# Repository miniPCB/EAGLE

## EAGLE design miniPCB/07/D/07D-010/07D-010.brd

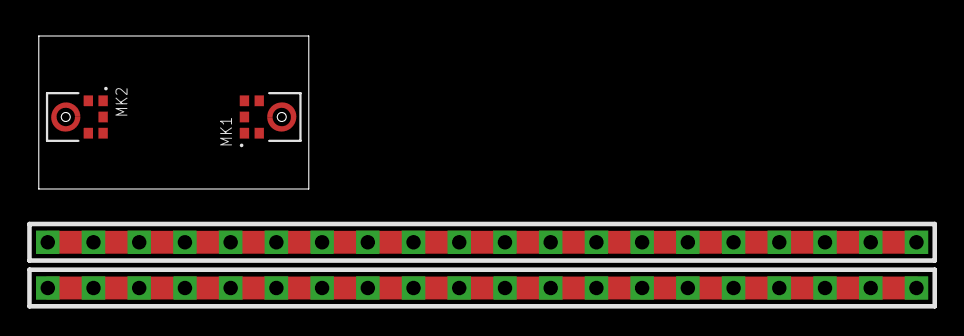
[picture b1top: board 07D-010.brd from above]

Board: 2 copper layers, 15.0 x 8.5 mm, 3 parts (0 on the bottom side), 2 nets, no tracks yet.

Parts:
MK1, MK2: SPH0645LM4H-B; MIC_SPH0645LM4H-B
U$1: BTM525; PINS_1_20P

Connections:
GND: MK1.3, MK2.3
VDD: MK1.5, MK2.5

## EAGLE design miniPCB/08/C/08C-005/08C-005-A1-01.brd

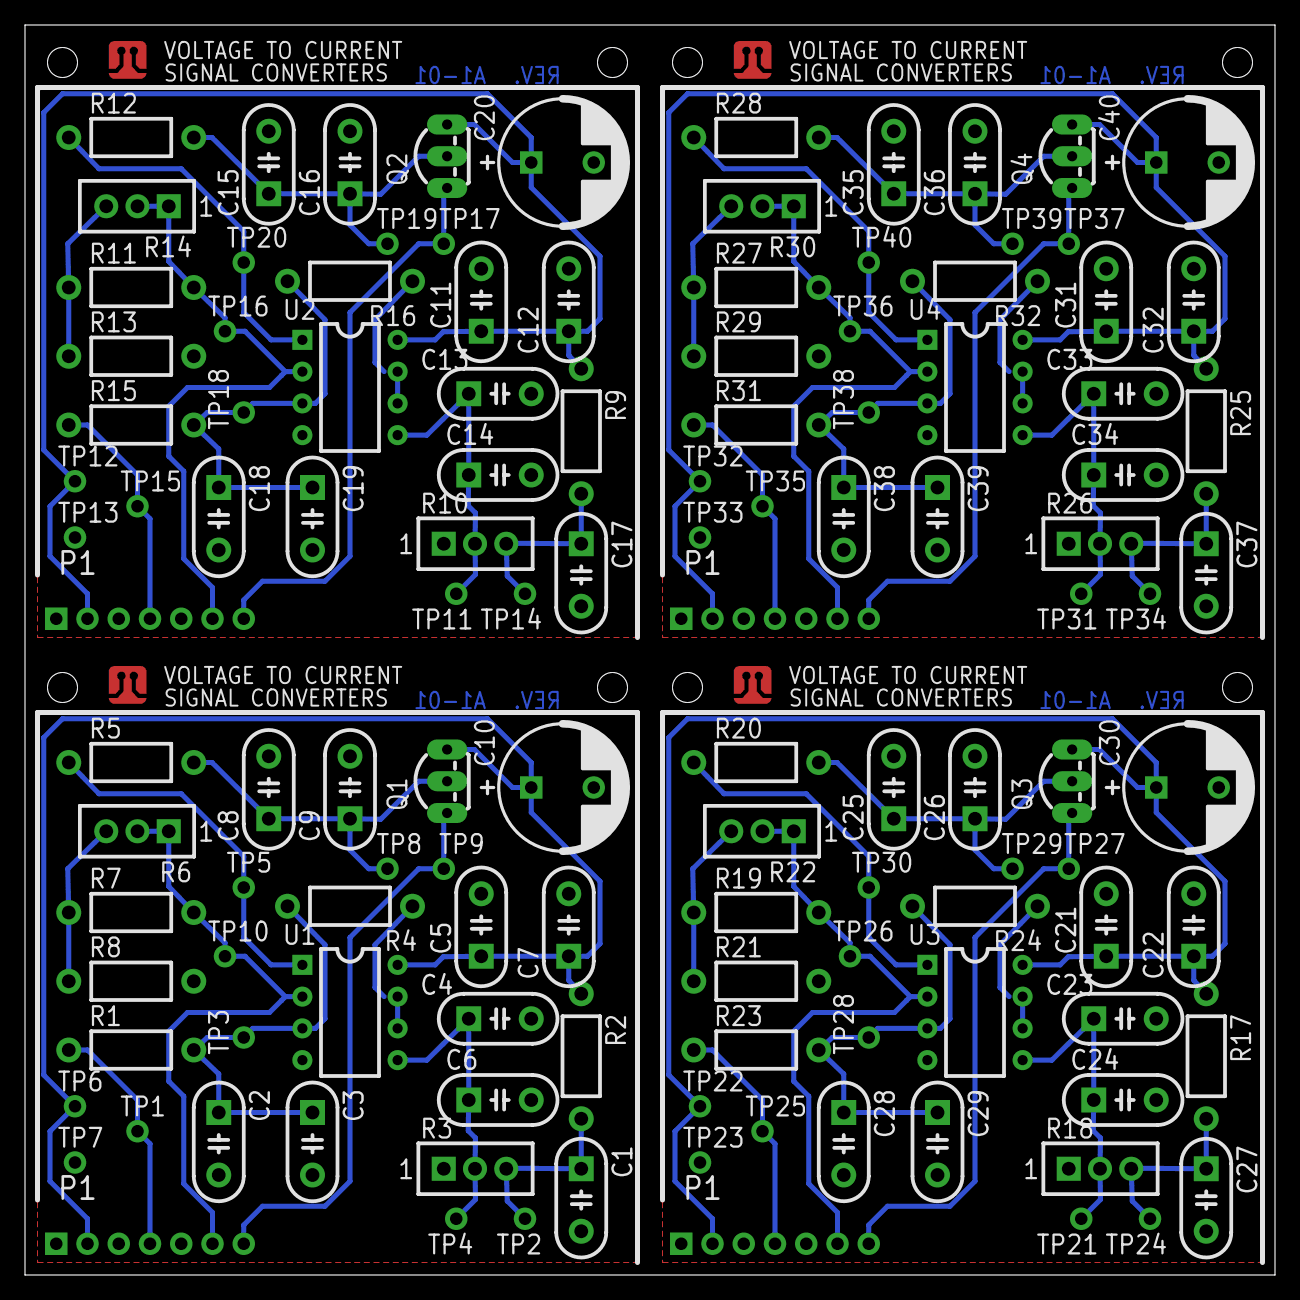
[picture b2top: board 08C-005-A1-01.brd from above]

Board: 2 copper layers, 100.0 x 100.0 mm, 129 parts (0 on the bottom side), 48 nets.

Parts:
C1, C2, C3, C4, C5, C6, C7, C8, C9, C11, C12, C13, C14, C15, C16, C17, C18, C19, C21, C22, C23, C24, C25, C26, C27, C28, C29, C31, C32, C33, C34, C35, C36, C37, C38, C39: C050-024X044
C10, C20, C30, C40: C5MM
E$1: MINIPCB_PANEL_IMAGEFRAME
P1, P2, P3, P4: PINS_1X7
PCB1, PCB2, PCB3, PCB4: MINIPCB_0P_50X50MM
Q1, Q2, Q3, Q4: TO92-EBC-OVAL
R1, R2, R4, R5, R7, R8, R9, R11, R12, R13, R15, R16, R17, R19, R20, R21, R23, R24, R25, R27, R28, R29, R31, R32: 0207/10
R3, R6, R10, R14, R18, R22, R26, R30: TRIM_0100
TP1, TP2, TP3, TP4, TP5, TP6, TP7, TP8, TP9, TP10, TP11, TP12, TP13, TP14, TP15, TP16, TP17, TP18, TP19, TP20, TP21, TP22, TP23, TP24, TP25, TP26, TP27, TP28, TP29, TP30, TP31, TP32, TP33, TP34, TP35, TP36, TP37, TP38, TP39, TP40: PINS_1_TESTPOINT_KE5000_NOTEXT
U1, U2, U3, U4: DIL08

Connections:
BIAS: C4.1, C6.1, R3.2, TP4.1, U1.5
BIAS1: C13.1, C14.1, R10.2, TP11.1, U2.5
BIAS2: C23.1, C24.1, R18.2, TP21.1, U3.5
BIAS3: C33.1, C34.1, R26.2, TP31.1, U4.5
GND: C1.2, C2.2, C3.2, C4.2, C5.2, C6.2, C7.2, C8.2, C9.2, C10.-, P1.1, P1.5, R3.1, R8.2, TP7.1, U1.4
GND1: C11.2, C12.2, C13.2, C14.2, C15.2, C16.2, C17.2, C18.2, C19.2, C20.-, P2.1, P2.5, R10.1, R13.2, TP13.1, U2.4
GND2: C21.2, C22.2, C23.2, C24.2, C25.2, C26.2, C27.2, C28.2, C29.2, C30.-, P3.1, P3.5, R18.1, R21.2, TP23.1, U3.4
GND3: C31.2, C32.2, C33.2, C34.2, C35.2, C36.2, C37.2, C38.2, C39.2, C40.-, P4.1, P4.5, R26.1, R29.2, TP33.1, U4.4
IN: R4.1, U1.6, U1.7
IN1: R16.1, U2.6, U2.7
IN2: R24.1, U3.6, U3.7
IN3: R32.1, U4.6, U4.7
unnamed: C2.1, C3.1, R1.2, R4.2, TP3.1, U1.3
unnamed: P1.4, R1.1, TP1.1
unnamed: P2.4, R15.1, TP15.1
unnamed: C18.1, C19.1, R15.2, R16.2, TP18.1, U2.3
unnamed: P3.4, R23.1, TP25.1
unnamed: C28.1, C29.1, R23.2, R24.2, TP28.1, U3.3
unnamed: P4.4, R31.1, TP35.1
unnamed: C38.1, C39.1, R31.2, R32.2, TP38.1, U4.3
OUT+: P1.7, Q1.E, TP9.1
OUT+1: P2.7, Q2.E, TP17.1
OUT+2: P3.7, Q3.E, TP27.1
OUT+3: P4.7, Q4.E, TP37.1
OUT-: P1.6, R6.1, R6.2, R7.2, TP10.1, U1.2
OUT-1: P2.6, R11.2, R14.1, R14.2, TP16.1, U2.2
OUT-2: P3.6, R19.2, R22.1, R22.2, TP26.1, U3.2
OUT-3: P4.6, R27.2, R30.1, R30.2, TP36.1, U4.2
Q1.B: C8.1, C9.1, Q1.B, R5.2, TP8.1
Q1.B1: C15.1, C16.1, Q2.B, R12.2, TP19.1
Q1.B2: C25.1, C26.1, Q3.B, R20.2, TP29.1
Q1.B3: C35.1, C36.1, Q4.B, R28.2, TP39.1
R2.1: C17.1, R9.2, R10.3, TP14.1
R2.2: C27.1, R17.2, R18.3, TP24.1
R2.3: C1.1, R2.2, R3.3, TP2.1
R2.4: C37.1, R25.2, R26.3, TP34.1
R6.1: R11.1, R13.1, R14.3
R6.2: R19.1, R21.1, R22.3
R6.3: R6.3, R7.1, R8.1
R6.4: R27.1, R29.1, R30.3
U1.1: R5.1, TP5.1, U1.1
U1.2: R12.1, TP20.1, U2.1
U1.3: R20.1, TP30.1, U3.1
U1.4: R28.1, TP40.1, U4.1
V+: C5.1, C7.1, C10.+, P1.2, Q1.C, R2.1, TP6.1, U1.8
V+1: C11.1, C12.1, C20.+, P2.2, Q2.C, R9.1, TP12.1, U2.8
V+2: C21.1, C22.1, C30.+, P3.2, Q3.C, R17.1, TP22.1, U3.8
V+3: C31.1, C32.1, C40.+, P4.2, Q4.C, R25.1, TP32.1, U4.8

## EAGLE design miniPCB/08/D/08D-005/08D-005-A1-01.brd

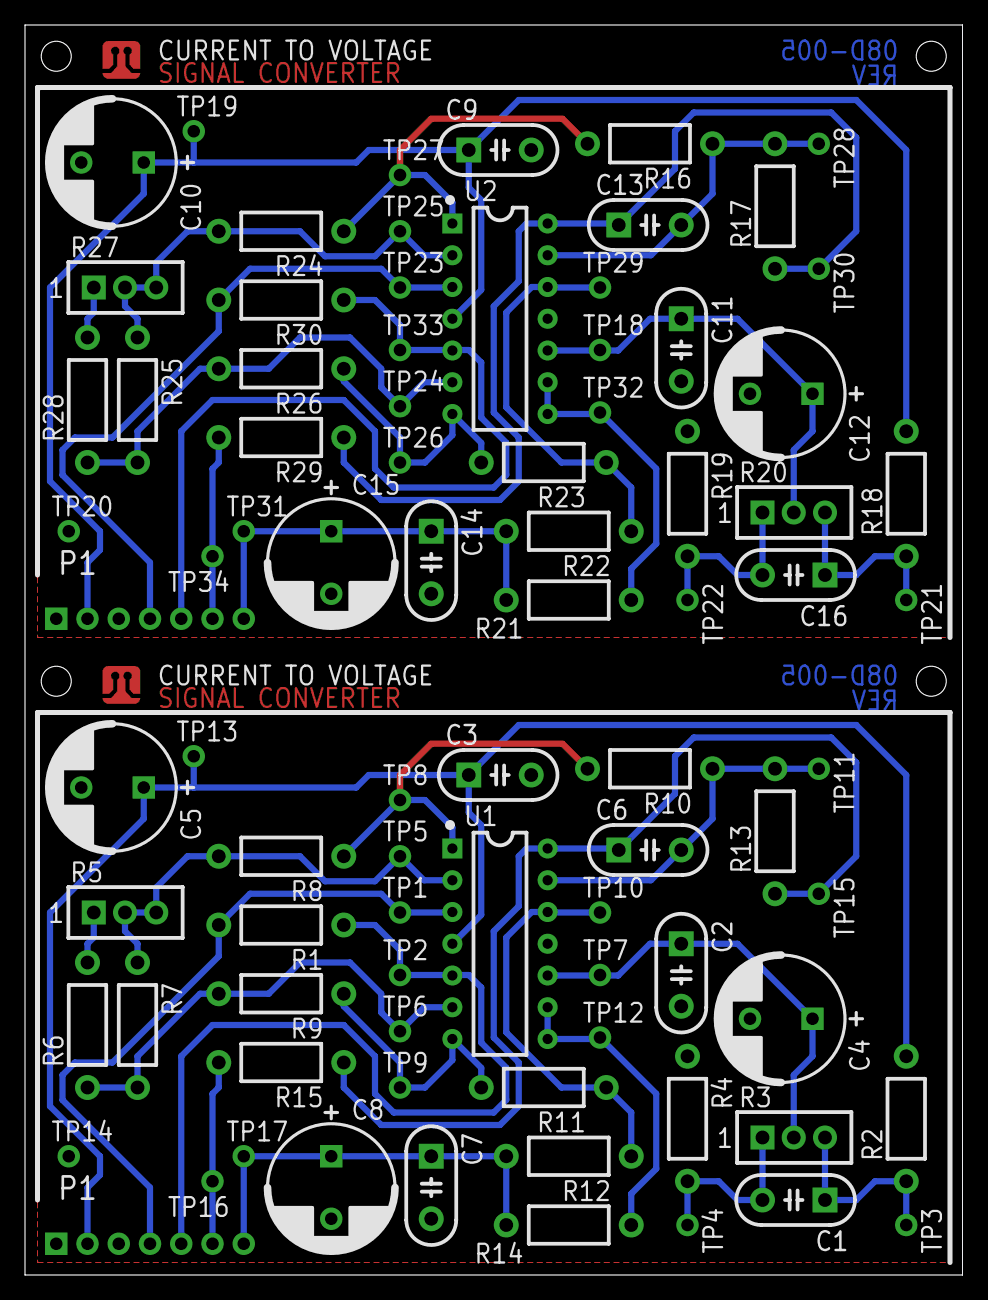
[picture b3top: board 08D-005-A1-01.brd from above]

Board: 2 copper layers, 75.0 x 100.0 mm, 87 parts (0 on the bottom side), 36 nets.

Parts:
C1, C2, C3, C6, C7, C9, C11, C13, C14, C16: C050-024X044
C4, C5, C8, C10, C12, C15: C5MM
E$1: MINIPCB_PANEL_IMAGEFRAME
P1, P2: PINS_1X7
PCB1, PCB2: MINIPCB_0P_50X75
R1, R2, R4, R6, R7, R8, R9, R10, R11, R12, R13, R14, R15, R16, R17, R18, R19, R21, R22, R23, R24, R25, R26, R28, R29, R30: 0207/10
R3, R5, R20, R27: TRIM_0100
TP1, TP2, TP3, TP4, TP5, TP6, TP7, TP8, TP9, TP10, TP11, TP12, TP13, TP14, TP15, TP16, TP17, TP18, TP19, TP20, TP21, TP22, TP23, TP24, TP25, TP26, TP27, TP28, TP29, TP30, TP31, TP32, TP33, TP34: PINS_1_TESTPOINT_KE5000_NOTEXT
U1, U2: DIL14

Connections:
BIAS: C2.1, C4.+, R3.2, TP7.1, U1.10
BIAS1: C11.1, C12.+, R20.2, TP18.1, U2.10
GND: C2.2, C3.2, C4.-, C5.-, C7.2, C8.-, P1.1, R4.1, TP14.1, U1.11
GND1: C9.2, C10.-, C11.2, C12.-, C14.2, C15.-, P2.1, R19.1, TP20.1, U2.11
unnamed: R11.1, R12.1, TP10.1, U1.12
unnamed: C7.1, C8.+, P1.7, R12.2, R14.2, TP17.1
unnamed: P1.5, R1.1, TP2.1, U1.5
unnamed: P1.4, R1.2, TP1.1, U1.3
unnamed: R5.2, R5.3, R7.1, R8.2, TP5.1, U1.2
unnamed: R6.1, R7.2, R9.2, TP6.1, U1.6
unnamed: R8.1, R10.2, TP8.1, U1.1
unnamed: R9.1, R11.2, TP9.1, U1.7
unnamed: R14.1, TP12.1, U1.8, U1.9
unnamed: R5.1, R6.2
unnamed: P1.6, R15.2, TP16.1
unnamed: R22.1, R23.1, TP29.1, U2.12
unnamed: C14.1, C15.+, P2.7, R21.2, R22.2, TP31.1
unnamed: P2.5, R30.1, TP33.1, U2.5
unnamed: P2.4, R30.2, TP23.1, U2.3
unnamed: R24.2, R25.1, R27.2, R27.3, TP25.1, U2.2
unnamed: R25.2, R26.2, R28.1, TP24.1, U2.6
unnamed: R16.2, R24.1, TP27.1, U2.1
unnamed: R23.2, R26.1, TP26.1, U2.7
unnamed: R21.1, TP32.1, U2.8, U2.9
unnamed: R27.1, R28.2
unnamed: P2.6, R29.2, TP34.1
OUT: C6.1, R13.1, R15.1, TP15.1, U1.14
OUT1: C13.1, R17.1, R29.1, TP30.1, U2.14
POT.1: C1.2, R3.1, R4.2, TP4.1
POT.2: C16.1, R18.1, R20.3, TP21.1
POT.3: C1.1, R2.1, R3.3, TP3.1
POT.4: C16.2, R19.2, R20.1, TP22.1
V+: C3.1, C5.+, P1.2, R2.2, TP13.1, U1.4
V+1: C9.1, C10.+, P2.2, R18.2, TP19.1, U2.4
VFB: C6.2, R10.1, R13.2, TP11.1, U1.13
VFB1: C13.2, R16.1, R17.2, TP28.1, U2.13

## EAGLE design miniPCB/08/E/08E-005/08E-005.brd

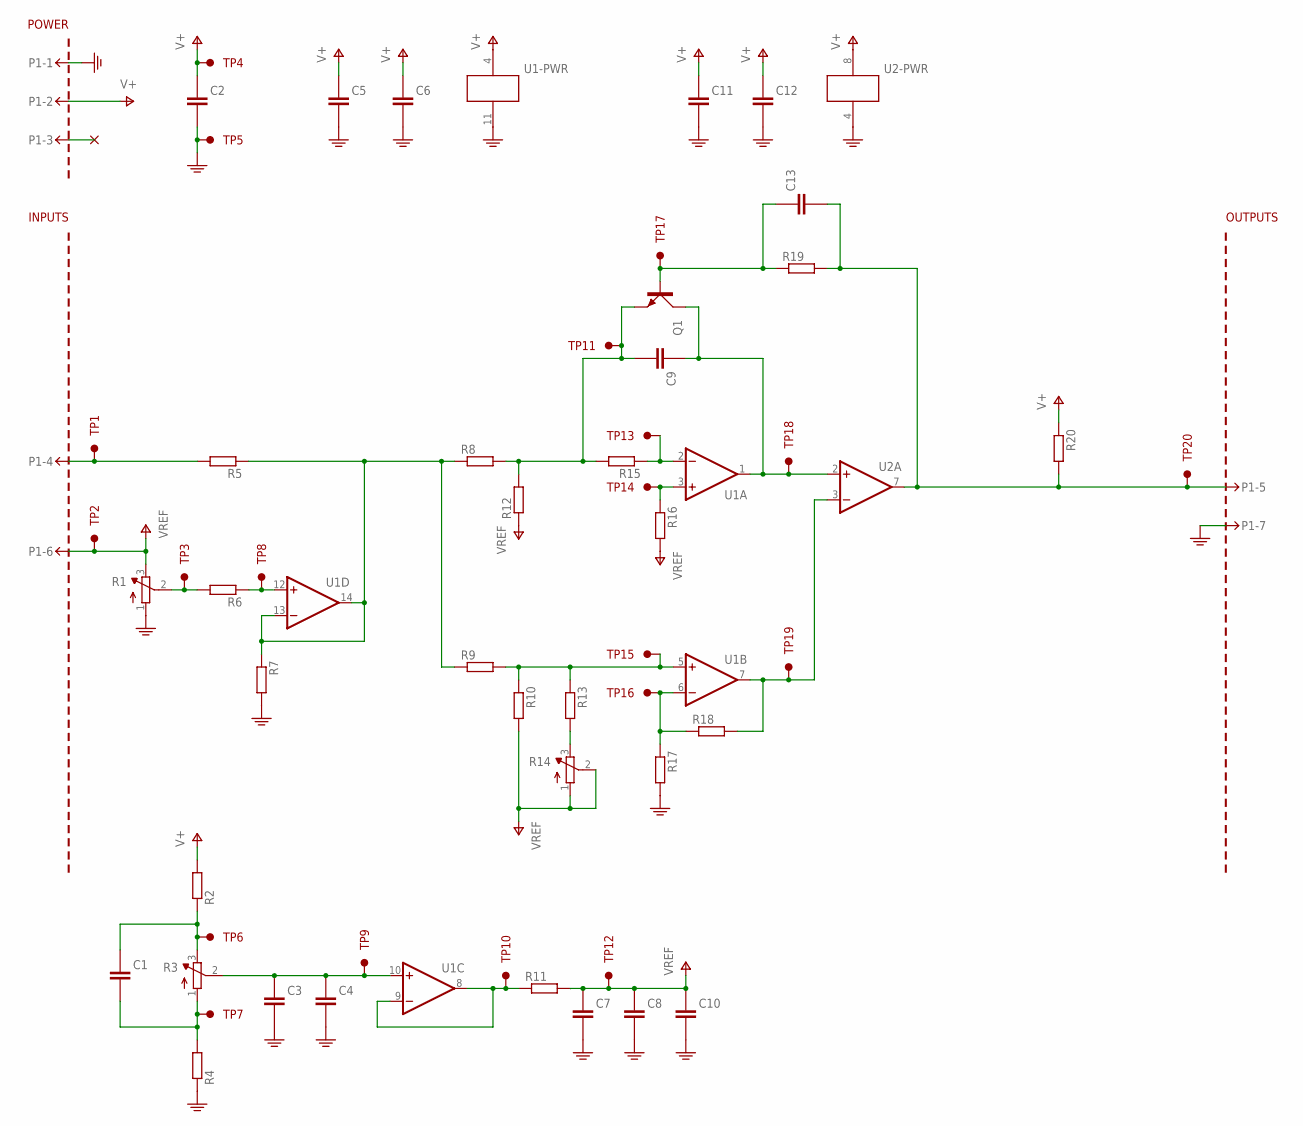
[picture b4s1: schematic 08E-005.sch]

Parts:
C1, C3, C4, C5, C6, C7, C8, C9, C11, C12, C13: CAPACITORTHD; C050-024X044
C2, C10: CAPACITOR_10; C5MM
P1-: MINIPCB_7P50X100; MINIPCB_7P_50X100; PART_NUMBER X08E-005-A
Q1: BJT_NPNEBC; TO92-EBC-OVAL
R1: TRIMPOT3386; TRIM-3386
R2, R4, R5, R6, R7, R8, R9, R10, R11, R12, R13, R15, R16, R17, R18, R19, R20: RESISTOR10MM; 0207/10
R3, R14: TRIMPOT0.100THD; TRIM_0100
TP1, TP2, TP3, TP4, TP5, TP6, TP7, TP8, TP9, TP10, TP11, TP12, TP13, TP14, TP15, TP16, TP17, TP18, TP19, TP20: TESTPOINTKE5000-SMTEXT; PINS_1_TESTPOINT_KE5000_NOTEXT
U1: OPAMP_QUADTHD; DIL14
U2: COMPARATOR_SINGLE_WITHBALANCETHD; DIL08

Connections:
BIAS: C3.1 (+), C4.1 (+), R3.2 (S), TP9.1, U1.10 (+IN)
GND: C2.-, C3.2 (-), C4.2 (-), C5.2 (-), C6.2 (-), C7.2 (-), C8.2 (-), C10.-, C11.2 (-), C12.2 (-), P1-.1, P1-.7, R1.1 (A), R4.1, R7.2, R17.2, TP5.1, U1.11 (V-), U2.4 (V-); also elsewhere on the board
unnamed: R16.1, TP14.1, U1.3 (+IN)
unnamed: R15.1, TP13.1, U1.2 (-IN)
unnamed: C9.2 (-), Q1.E, R8.2, R12.2, R15.2, TP11.1
unnamed 5: C13.2 (-), P1-.5, R19.2, R20.2, TP20.1, U2.7 (OUT); also elsewhere on the board
unnamed: C9.1 (+), Q1.C, TP18.1, U1.1 (OUT), U2.2 (+IN)
unnamed: C13.1 (+), Q1.B, R19.1, TP17.1
unnamed: R11.1, TP10.1, U1.8 (OUT), U1.9 (-IN)
unnamed: R17.1, R18.1, TP16.1, U1.6 (-IN)
unnamed: R18.2, TP19.1, U1.7 (OUT), U2.3 (-IN)
unnamed: R6.1, TP8.1, U1.12 (+IN)
unnamed: R1.2 (S), R6.2, TP3.1
unnamed: R9.2, R10.1, R13.1, TP15.1, U1.5 (+IN)
unnamed: R13.2, R14.3 (E)
POT.1: C1.2 (-), R3.1 (A), R4.2, TP7.1
POT.3: C1.1 (+), R2.1, R3.3 (E), TP6.1
V+: C2.+, C5.1 (+), C6.1 (+), C11.1 (+), C12.1 (+), P1-.2, R2.2, R20.1, TP4.1, U1.4 (V+), U2.8 (V+); also elsewhere on the board
VREF: C7.1 (+), C8.1 (+), C10.+, P1-.6, R1.3 (E), R10.2, R11.2, R12.1, R14.1 (A), R14.2 (S), R16.2, TP2.1, TP12.1; also elsewhere on the board

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
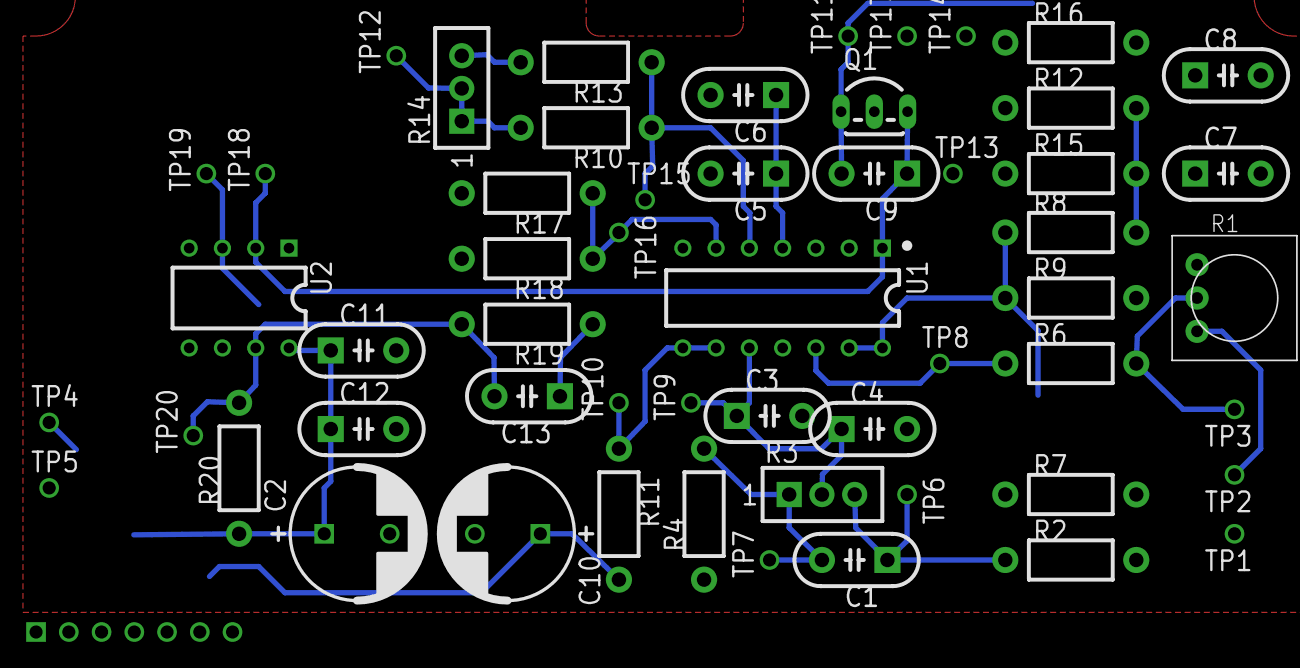
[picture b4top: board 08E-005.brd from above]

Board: 2 copper layers, 57 parts (0 on the bottom side), 20 nets.

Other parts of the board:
P1: PINS_1X7
PCB1: POWER; MINIPCB_0P_50X75

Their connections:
GND: P1.1, P1.5, P1.7; also elsewhere on the board
unnamed 5: P1.6; also elsewhere on the board
V+: P1.2; also elsewhere on the board
VREF: P1.4; also elsewhere on the board

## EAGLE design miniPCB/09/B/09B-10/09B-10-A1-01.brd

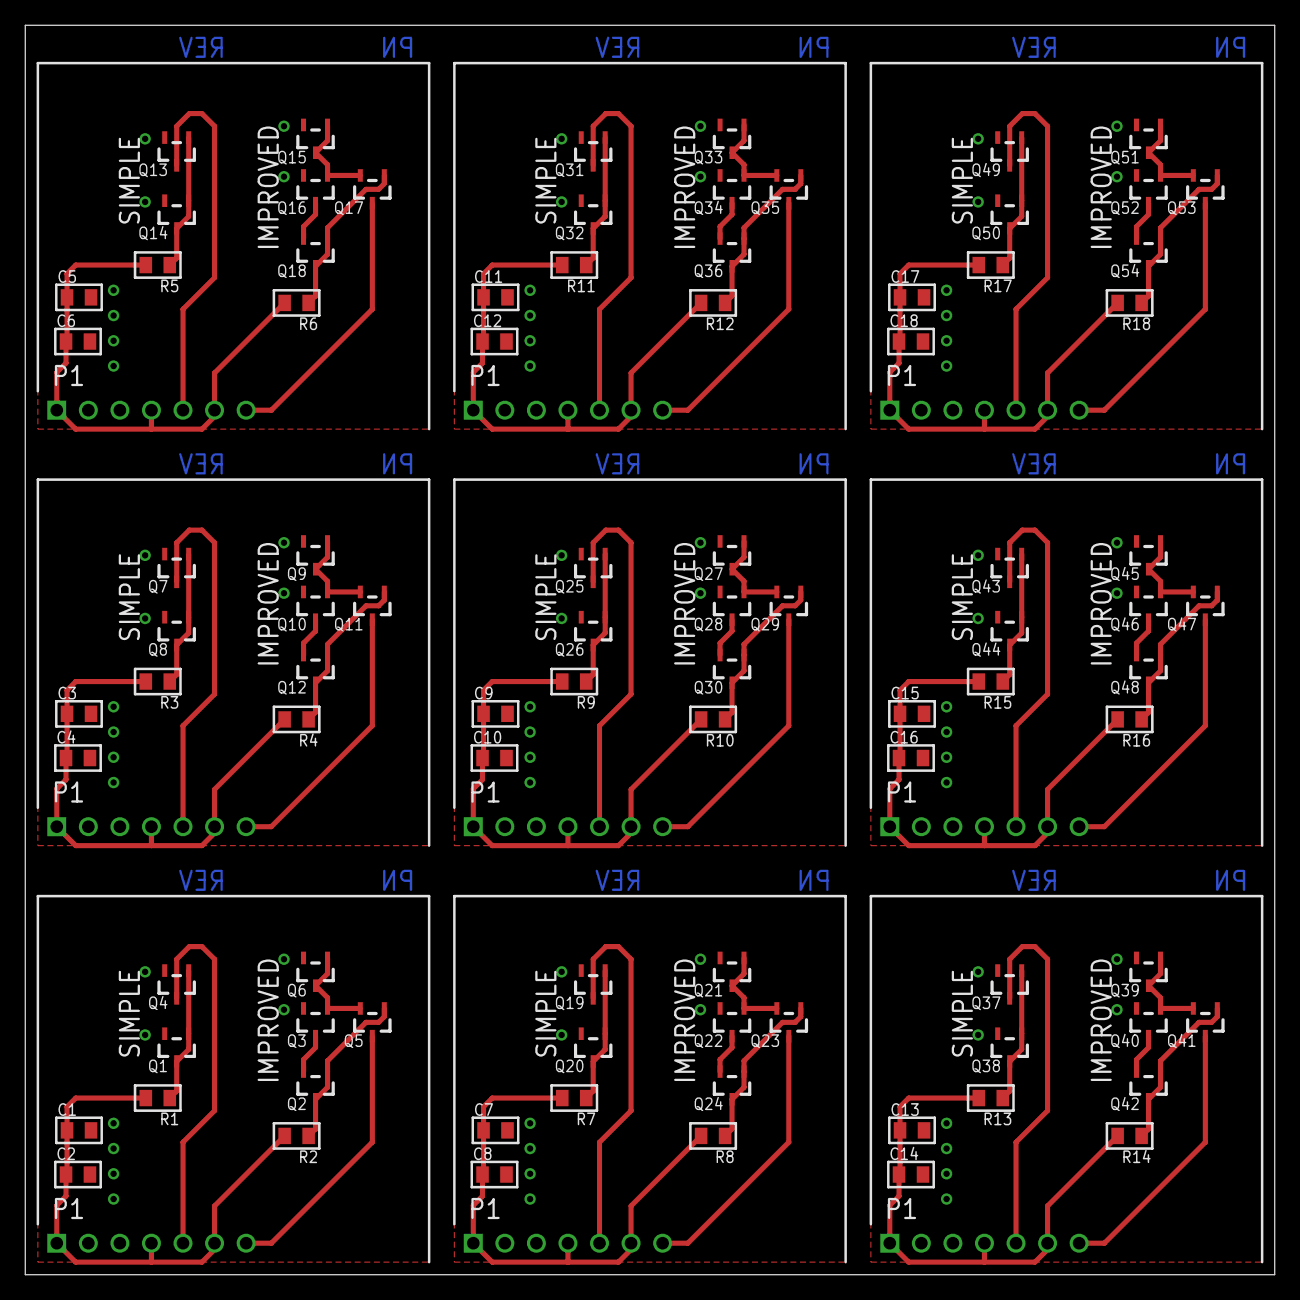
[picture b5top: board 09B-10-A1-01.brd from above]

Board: 2 copper layers, 99.0 x 99.0 mm, 108 parts (0 on the bottom side), 72 nets.

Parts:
C1, C2, C3, C4, C5, C6, C7, C8, C9, C10, C11, C12, C13, C14, C15, C16, C17, C18: C0805
P1, P2, P3, P4, P5, P6, P7, P8, P9: PINS_1X7
PCB1, PCB2, PCB3, PCB4, PCB5, PCB6, PCB7, PCB8, PCB9: PCB33
Q1, Q2, Q3, Q4, Q5, Q6, Q7, Q8, Q9, Q10, Q11, Q12, Q13, Q14, Q15, Q16, Q17, Q18, Q19, Q20, Q21, Q22, Q23, Q24, Q25, Q26, Q27, Q28, Q29, Q30, Q31, Q32, Q33, Q34, Q35, Q36, Q37, Q38, Q39, Q40, Q41, Q42, Q43, Q44, Q45, Q46, Q47, Q48, Q49, Q50, Q51, Q52, Q53, Q54: SOT23
R1, R2, R3, R4, R5, R6, R7, R8, R9, R10, R11, R12, R13, R14, R15, R16, R17, R18: R0805

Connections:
GND: C1.2ASDF, C2.2ASDF, P1.2, Q1.2, Q3.2, Q4.2, Q6.2
GND1: C3.2ASDF, C4.2ASDF, P2.2, Q7.2, Q8.2, Q9.2, Q10.2
GND2: C5.2ASDF, C6.2ASDF, P3.2, Q13.2, Q14.2, Q15.2, Q16.2
GND3: C7.2ASDF, C8.2ASDF, P4.2, Q19.2, Q20.2, Q21.2, Q22.2
GND4: C9.2ASDF, C10.2ASDF, P5.2, Q25.2, Q26.2, Q27.2, Q28.2
GND5: C11.2ASDF, C12.2ASDF, P6.2, Q31.2, Q32.2, Q33.2, Q34.2
GND6: C13.2ASDF, C14.2ASDF, P7.2, Q37.2, Q38.2, Q39.2, Q40.2
GND7: C15.2ASDF, C16.2ASDF, P8.2, Q43.2, Q44.2, Q45.2, Q46.2
GND8: C17.2ASDF, C18.2ASDF, P9.2, Q49.2, Q50.2, Q51.2, Q52.2
unnamed: Q1.1, Q1.3, Q4.1, R1.1
unnamed: P1.5, Q4.3
unnamed: Q3.1, Q5.2, Q6.1, Q6.3
unnamed: Q2.1, Q2.3, Q5.1, R2.1
unnamed: Q2.2, Q3.3
unnamed: Q7.1, Q8.1, Q8.3, R3.1
unnamed: P1.7, Q5.3
unnamed: P2.5, Q7.3
unnamed: Q9.1, Q9.3, Q10.1, Q11.2
unnamed: Q11.1, Q12.1, Q12.3, R4.1
unnamed: Q10.3, Q12.2
unnamed: P2.7, Q11.3
unnamed: Q13.1, Q14.1, Q14.3, R5.1
unnamed: P3.5, Q13.3
unnamed: Q15.1, Q15.3, Q16.1, Q17.2
unnamed: Q17.1, Q18.1, Q18.3, R6.1
unnamed: Q16.3, Q18.2
unnamed: P3.7, Q17.3
unnamed: Q19.1, Q20.1, Q20.3, R7.1
unnamed: P4.5, Q19.3
unnamed: Q21.1, Q21.3, Q22.1, Q23.2
unnamed: Q23.1, Q24.1, Q24.3, R8.1
unnamed: Q22.3, Q24.2
unnamed: P4.7, Q23.3
unnamed: Q25.1, Q26.1, Q26.3, R9.1
unnamed: P5.5, Q25.3
unnamed: Q27.1, Q27.3, Q28.1, Q29.2
unnamed: Q29.1, Q30.1, Q30.3, R10.1
unnamed: Q28.3, Q30.2
unnamed: P5.7, Q29.3
unnamed: Q31.1, Q32.1, Q32.3, R11.1
unnamed: P6.5, Q31.3
unnamed: Q33.1, Q33.3, Q34.1, Q35.2
unnamed: Q35.1, Q36.1, Q36.3, R12.1
unnamed: Q34.3, Q36.2
unnamed: P6.7, Q35.3
unnamed: Q37.1, Q38.1, Q38.3, R13.1
unnamed: P7.5, Q37.3
unnamed: Q39.1, Q39.3, Q40.1, Q41.2
unnamed: Q41.1, Q42.1, Q42.3, R14.1
unnamed: Q40.3, Q42.2
unnamed: P7.7, Q41.3
unnamed: Q43.1, Q44.1, Q44.3, R15.1
unnamed: P8.5, Q43.3
unnamed: Q45.1, Q45.3, Q46.1, Q47.2
unnamed: Q47.1, Q48.1, Q48.3, R16.1
unnamed: Q46.3, Q48.2
unnamed: P8.7, Q47.3
unnamed: Q49.1, Q50.1, Q50.3, R17.1
unnamed: P9.5, Q49.3
unnamed: Q51.1, Q51.3, Q52.1, Q53.2
unnamed: Q53.1, Q54.1, Q54.3, R18.1
unnamed: Q52.3, Q54.2
unnamed: P9.7, Q53.3
V+: C1.1ASD, C2.1ASD, P1.1, P1.4, P1.6, R1.2, R2.2
V+1: C3.1ASD, C4.1ASD, P2.1, P2.4, P2.6, R3.2, R4.2
V+2: C5.1ASD, C6.1ASD, P3.1, P3.4, P3.6, R5.2, R6.2
V+3: C7.1ASD, C8.1ASD, P4.1, P4.4, P4.6, R7.2, R8.2
V+4: C9.1ASD, C10.1ASD, P5.1, P5.4, P5.6, R9.2, R10.2
V+5: C11.1ASD, C12.1ASD, P6.1, P6.4, P6.6, R11.2, R12.2
V+6: C13.1ASD, C14.1ASD, P7.1, P7.4, P7.6, R13.2, R14.2
V+7: C15.1ASD, C16.1ASD, P8.1, P8.4, P8.6, R15.2, R16.2
V+8: C17.1ASD, C18.1ASD, P9.1, P9.4, P9.6, R17.2, R18.2
